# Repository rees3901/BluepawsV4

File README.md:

# Bluepaws V4

Unified firmware repository for the Bluepaws animal tracker system. Both the transmitting collar and receiving home hub share a single codebase with a common TLV binary protocol and configuration library.

## System Overview

| Component | MCU | Radio | Connectivity |
|-----------|-----|-------|-------------|
| **Collar** | nRF52840 | SX1262 LoRa | Sequans Monarch 2 GM02SP (LTE-M/NB-IoT + GNSS), BLE |
| **Home Hub** | ESP32-S3 | SX1262 LoRa | WiFi, BLE beacon |

**Data paths:**
- Collar -> LoRa -> Home Hub -> log + display -> WiFi -> Cloud
- Collar -> LTE-M/NB-IoT -> Cloud via REST POST

**Battery target:** 30+ days at 10-minute wake intervals.

## Hardware

| Part | Role | Key Specs |
|------|------|-----------|
| **nRF52840** (Seeed XIAO BLE Sense) | Collar MCU | ARM Cortex-M4F, BLE 5.0, 256KB RAM |
| **SX1262** | LoRa transceiver | 150 MHz-960 MHz, +22 dBm, LoRa/FSK |
| **[Sequans Monarch 2 GM02SP](https://sequans.com/products/monarch-2-gm02s/)** | Cellular + GNSS | LTE Cat M1/NB-IoT, integrated GNSS, 1uA deep sleep, 23 dBm TX, EAL5+ secure enclave, iSIM, single 2.2V rail, global bands |
| **ESP32-S3** (Seeed XIAO) | Hub MCU | Dual-core, WiFi, BLE 5.0, 512KB SRAM |

The Sequans GM02SP replaces the previous BG77 + L76K combination. A single module handles both cellular IoT and GPS positioning, simplifying the collar BOM and reducing power draw.

### Independent Walter LTE testbed

The separate `walter` PlatformIO target exercises real GM02SP LTE/GNSS on an
ESP32-S3 Walter board, with a simulated LoRa transmit step and its own independent
collar ID **1010**. It does not replace or alter the WisMesh collar firmware.
See [Walter setup and commissioning](docs/firmware/collar/WALTER_LTE_TESTBED.md) before provisioning
credentials or flashing. It boots idle and is not a default build/upload target.

## Repository Structure

The top level is organised by responsibility. Firmware stays under the physical
product it runs on; the two Home Hub implementations are grouped together so
that `hub` and `home-hub` no longer appear to be separate products.

```text
BluepawsV4/
├── README.md                         # Repository overview
├── docs/
│   ├── protocol/                     # Wire formats and commands
│   ├── firmware/collar/              # Collar design and test notes
│   ├── firmware/home-hub/            # Home Hub design and test notes
│   ├── operations/                   # Runbooks and release readiness
│   └── development/                  # Environment strategy and backlog
├── pcb/collar/                       # Collar PCB projects and vendor libraries
├── platformio.ini                    # Multi-environment build config
├── shared/lib/BluepawsProtocol/      # Shared protocol & config
│   ├── README.md                     # Protocol implementation notes
│   ├── library.json                  # PlatformIO library manifest
│   ├── bp_protocol.h                 # Shared protocol implementation header
│   └── bp_config.h                   # LoRa params, profiles, timing
├── collar/                           # nRF52840 collar firmware
│   ├── src/main.cpp
│   └── include/collar_pins.h
├── hub/                              # All Home Hub implementations
│   ├── platformio/                   # Heltec ESP32-S3 prototype + LittleFS UI
│   ├── esp-idf-p4/                   # ESP32-P4 production testbed
│   ├── maps/                         # Offline map-pack inputs and guidance
│   └── tests/esp-idf-p4/             # Host tests for the P4 core
├── diagnostics/
│   ├── t190-radio-monitor/           # Passive LoRa/TLV receiver (formerly sniffer)
│   └── rak3272s-bluepaws-test/       # UART2/P2P bench test and TLV heartbeat
├── tools/
│   ├── mock-server.js                # Node.js mock hub for local GUI dev
│   ├── vps_position_simulator.py     # Legacy JSON HTTPS simulator
│   ├── tlv_telemetry_simulator.py    # Headless TLV fleet simulator
│   ├── tlv_packet_codec.py           # Shared v1.2 packet/wrapper codec
│   └── tlv_simulator_gui.py          # Desktop TLV test console
├── web/                              # Next.js + TypeScript customer dashboard
│   ├── src/app/                      # App Router entry point
│   ├── src/components/               # React dashboard and Leaflet map
│   ├── src/data/                     # Typed development telemetry
│   └── src/lib/telemetry.ts          # Future Supabase adapter boundary
├── mock_server.py                    # Python mock server (legacy)
└── supabase/                         # Cloud schema, migrations, and Edge Functions
```

## Web GUI

The hub serves a real-time tracking dashboard over WiFi, built with Leaflet.js and Server-Sent Events (SSE).

**Device Cards** - each tracked animal gets a card in the left sidebar showing:
- Unique emoji avatar with colour-coded ring (auto-assigned per device)
- Last GPS coordinates in monospace
- Status badge (Home / Out / Lost / Error)
- Telemetry grid: profile, battery %, signal strength, GPS accuracy, distance from home, last seen
- **Jump** - centres map on the animal at zoom 17
- **Follow** - auto-pans the map as new positions arrive
- **Trail** - toggles breadcrumb polyline on/off per device
- **Cmd** - opens command modal

**Map Features:**
- Three base layers: Street (OSM), Satellite (Esri), Topographic
- Per-device coloured trail lines with dashed polylines
- Lost-mode markers pulse red
- Measurement tool
- Dark / light theme toggle

**Connection Monitoring:**
- Server sends SSE heartbeat every 5 seconds
- Client watchdog flips to "No heartbeat" if 10 seconds pass without any event
- Status banner shows Connected or Disconnected

## Mock Server

Simulates animals with live SSE telemetry for local GUI development:

```bash
node tools/mock-server.js
# http://localhost:3000
# Streams position updates every 2s + heartbeat every 5s
```

## Customer Web App

`web/` contains the Vercel-ready Next.js and TypeScript refactor of the hub dashboard. It preserves the embedded GUI in `hub/platformio/data/`, reads the latest live positions from Supabase by default, and confines mock telemetry to tutorial mode.

```bash
cd web
npm install
npm run dev
```

For Vercel, import this repository and select `web` as the project **Root Directory**. Leave the Install, Build, and Output settings at their detected Next.js defaults. See `web/README.md` for the exact deployment settings and the planned HTTPS Edge Function -> Supabase -> Realtime data path.

The cloud ingestion schema, device registry, and authenticated Edge Function are under `supabase/`. See `tools/VPS_SIMULATOR.md` for the Ubuntu VPS client and `tools/TLV_SIMULATOR_GUI.md` for the desktop packet-builder and manual HTTPS test console.

## Development and Production Environments

The existing Supabase `BluepawsV4` project is the permanent DEV/Test environment. Production will use a separate clean Supabase project reconstructed from the version-controlled migrations in this repository. Development and simulator data must not be migrated into production.

The same GitHub repository and Vercel project are used for both environments, with Vercel environment configuration selecting the appropriate Supabase project.

See:

- [`docs/development/DEV_TO_PROD_STRATEGY.md`](docs/development/DEV_TO_PROD_STRATEGY.md) for the authoritative promotion strategy and decision record.
- [`docs/development/ENVIRONMENT_MATRIX.md`](docs/development/ENVIRONMENT_MATRIX.md) for DEV vs PROD separation rules.
- [`docs/operations/PRODUCTION_READINESS_CHECKLIST.md`](docs/operations/PRODUCTION_READINESS_CHECKLIST.md) for the pre-launch security and operational checklist.

## TLV Protocol v1.2

The canonical protocol document is:

```text
docs/protocol/TLV_PROTOCOL_V1_2.md
```

The system is moving away from production JSON telemetry. JSON remains useful for debugging, logs, exports and admin APIs, but LoRa and cellular telemetry should use the compact binary TLV packet.

Locked packet shape:

```text
[32-byte fixed header][0-24 bytes TLV][8-byte HMAC-SHA256 tag]
```

Packet size:

```text
minimum = 40 bytes
maximum = 64 bytes
```

### Fixed header summary

| Offset | Size | Field | Type | Notes |
|---:|---:|---|---|---|
| 0 | 1 | `ver` | u8 | Protocol version |
| 1 | 2 | `device_guid16` | u16 | Immutable collar identity |
| 3 | 2 | `msg_seq_id` | u16 | Per-device rolling sequence |
| 5 | 4 | `time_unix` | u32 | UTC timestamp |
| 9 | 1 | `state` | u8 | Packed status + power profile |
| 10 | 1 | `flags` | u8 | Core bitfield |
| 11 | 1 | `tx_reason` | u8 | Transmission reason enum |
| 12 | 4 | `lat_e7` | i32 | Latitude x 10000000 |
| 16 | 4 | `lon_e7` | i32 | Longitude x 10000000 |
| 20 | 2 | `batt_mV` | u16 | Battery voltage |
| 22 | 2 | `acc_m` | u16 | Accuracy in metres |
| 24 | 2 | `fix_age_s` | u16 | GNSS fix age |
| 26 | 1 | `sat_count` | u8 | Satellite count |
| 27 | 4 | `hdr_rsvd` | u8[4] | Reserved, set 0 |
| 31 | 1 | `tlv_len` | u8 | 0-24 TLV bytes |

The 8-byte tag is the first eight bytes of HMAC-SHA256 over the complete header
and TLV section. The same authenticated binary packet is preserved across LoRa
and LTE paths; path-specific RF and gateway details live only in the HTTPS JSON
wrapper. See the canonical document for enums, selected TLVs, validation rules
and examples.

## Message Flow

```text
Collar --LoRa--> Hub --REST POST--> Cloud
Collar --LTE-M/Cat-M1 REST POST--> Cloud
```

Both paths preserve the original authenticated packet, including `(device_guid16, msg_seq_id, time_unix)`. The hub relays the collar bytes without changing them. Redundancy is intentional for reliability.

Canonical retry deduplication is handled in the cloud using:

```text
SHA-256(complete authenticated packet)
```

Reuse of `(device_guid16, msg_seq_id, time_unix)` with different packet content
is treated as an identity conflict rather than an overwrite.

Hub CSV or debug log format should be derived from decoded TLV fields, not treated as the production on-air format.

## Building

Requires [PlatformIO](https://platformio.org/).

```bash
# Build both targets
pio run

# Build collar only
pio run -e collar

# Build hub only
pio run -e hub

# Upload to connected device
pio run -e collar -t upload
pio run -e hub -t upload
```

## Operating Profiles

| Profile | TX Power | Interval | Cellular | Remarks |
|---------|----------|----------|----------|---------|
| **Normal** | 19 dBm | 10 min | 1:10 | Daily tracking, balanced power and update frequency |
| **PowerSave** | 10 dBm | 30 min | 1:30 | At home or battery conservation, reduced TX power and longer sleep |
| **Active Find** | 19 dBm | 1 min | 1:5 | Cat is outside geofence or user is actively searching |
| **Emergency Lost** | 22 dBm | 30 s | 1:3 | User needs frequent updates for retrieval, then fallback to Active Find |

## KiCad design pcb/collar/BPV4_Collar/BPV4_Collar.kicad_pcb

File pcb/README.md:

# PCB Hardware

KiCad projects and their supporting component models are grouped by product.

For GM02SP, GNSS/LTE antenna, and modem power decisions, start with the
[Walter/GM02SP source guide](../docs/firmware/collar/WALTER_GM02SP_UPSTREAM_REFERENCE.md).
Its Walter board specifications must be checked against the bare GM02SP and the
production collar schematic before being used as PCB requirements.

The approved forward power design is the
[nPM1300 collar power architecture](../docs/hardware/collar/NPM1300_POWER_ARCHITECTURE.md).
It replaces the BQ24074, TPS62840 and MAX17048 architecture still present in the
current KiCad schematic; follow its verification gates during migration.

- `collar/` — BluePaws V4 collar main board, second board, evaluation layouts,
  plots, reports, symbols, footprints, 3D models, and retained vendor source
  packages.

The vendor assets have deliberately been retained. Some appear duplicated
because they preserve the original package or tool format used by an existing
KiCad project; deduplication should only happen after KiCad library references
are audited interactively.

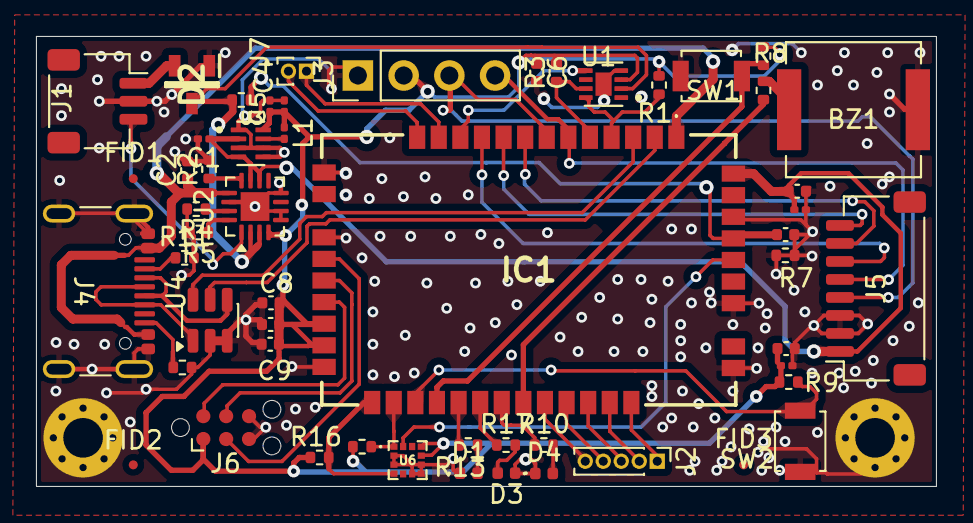
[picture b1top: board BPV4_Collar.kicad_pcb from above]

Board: 2 copper layers, 50.0 x 25.0 mm, 56 parts (0 on the bottom side), 49 nets.

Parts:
BZ1: CPT-7502-65-SMT-TR; XDCR_CPT-7502-65-SMT-TR
C1: C 10uF; C_0201_0603Metric
C2, C8: 1uF; C_0402_1005Metric
C3, C9, C10, C12, C13: 100nF; C_0402_1005Metric
C4, C5, C11, C14: 10uF; C_0201_0603Metric
C6: C 100nF; C_0402_1005Metric
D1, D3, D4: LED; LED_0402_1005Metric
D2: DMG2305UX-13; SOT96P240X120-3N
FID1, FID2, FID3: Fiducial; Fiducial_0.5mm_Mask1mm
IC1: RAK4630
J1: Conn_01x03; JST_SH_SM03B-SRSS-TB_1x03-1MP_P1.00mm_Horizontal
J2: Conn_01x05; PinHeader_1x05_P1.00mm_Vertical
J3: Conn_01x04; PinHeader_1x04_P2.54mm_Vertical
J4: USB_C_Receptacle_USB2.0_14P; USB_C_Receptacle_GCT_USB4105-xx-A_16P_TopMnt_Horizontal
J5: Conn_01x08; JST_SH_SM08B-SRSS-TB_1x08-1MP_P1.00mm_Horizontal
J6: Conn_01x06; Tag-Connect_TC2030-IDC-NL_2x03_P1.27mm_Vertical
J7: Conn_01x02_Pin; PinHeader_1x02_P1.00mm_Vertical
L1: 2.2uH; L_0201_0603Metric
MH1, MH2: M2_Screw; MountingHole_2.2mm_M2_Pad_Via
R1, R3: 4.7k; R_0402_1005Metric
R2, R5, R10, R13, R14, R17: 1k; R_0402_1005Metric
R4, R8, R9, R15, R16: 10k; R_0402_1005Metric
R6, R7: 1M; R_0402_1005Metric
R11, R12: 5.1k; R_0402_1005Metric
SW1, SW2: SW_Push; SW_SPST_B3U-1000P
U1: MAX17048G_T10; SON50P200X200X80-9N
U2: BQ24074RGT; VQFN-16-1EP_3x3mm_P0.5mm_EP1.6x1.6mm
U3: TPS62840DLCR; SON50P200X150X100-8N
U4: USBLC6-2SC6; SOT-23-6
U6: LIS2DW12TR; LGA12R50P4X4_200X200X70

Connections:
Accel: IC1.40 (P0.05/AIN3), U6.12 (INT1)
BATT_ALERT: IC1.11 (P0.21/UART1_DE), U1.5 (~ALERT)
BATT_I2C_SCL: IC1.5 (P0.14/I2C_SCL), R3.1, U1.7 (SCL)
BATT_I2C_SDA: IC1.4 (P0.13/I2C_SDA), R1.2, U1.8 (SDA)
BATT_NTC: J1.3, U2.1 (TS)
GM02SP_PS_STATUS: IC1.10 (P0.20/UART1_TX_(AT_COMMAND)), J5.6
GM02SP_RESET: IC1.9 (P0.19/UART1_RX_(AT_COMMAND)), J5.8
GND: BZ1.1, C1.2, C2.2, C3.2, C4.2, C5.2, C6.2, C8.2, C9.2, C10.2, C11.2, C12.2, C13.2, C14.2, D1.1 (K), D2.1 (G), D3.1 (K), D4.1 (K), IC1.14 (GND_1), IC1.16 (GND_2), IC1.22 (GND_3), IC1.36 (GND_5), IC1.38 (GND_6), IC1.42 (GND_7), J1.2, J3.1, J4.A1 (GND), J4.A12 (GND), J4.B1 (GND), J4.B12 (GND), J4.S1 (SHIELD), J5.2, J5.3, J6.5, J6.6, MH1.1, MH2.1, R2.2, R4.2, R5.2, R7.1, R7.2, R11.2, R12.2, SW1.2 (A), SW2.1 (K), U1.4 (GND), U1.9 (EP), U2.5 (EN2), U2.6 (EN1), U2.8 (VSS), U2.14 (TMR), U2.17 (VSS), U3.1 (GND), U3.3 (MODE), U3.5 (VSET), U3.6 (STOP), U4.2 (GND), U4.3 (I/O2), U6.2 (CS), U6.3 (SDO/SA0), U6.6 (GND), U6.7 (RES), U6.8 (GND)
NRF_RESET: IC1.17 (NRF_RESET), J6.3
unnamed: BZ1.2, R14.2
unnamed: D1.2 (A), R13.2
unnamed: D3.2 (A), R17.2
unnamed: D4.2 (A), R10.2
unnamed: IC1.35 (GND_4), J2.1
unnamed: IC1.30 (P0.02/QSPI_DIO3), R14.1
unnamed: IC1.29 (P0.03/QSPI_CLK), R10.1
unnamed: IC1.13 (P0.09/NFC1), J7.2
unnamed: IC1.12 (P0.10/NFC2), J7.1
unnamed: IC1.23 (P0.24/I2C_SDA_2), R16.2, U6.4 (SDA/SDI/SDO)
unnamed: IC1.24 (P0.25/I2C_SCL_2), R15.2, U6.1 (SCL/SPC)
unnamed: IC1.34 (P0.26/QSPI_CS), J2.2
unnamed: IC1.31 (P0.28/QSPI_DIO2), J2.5
unnamed: IC1.32 (P0.29/QSPI_DIO1), J2.4
unnamed: IC1.33 (P0.30/QSPI_DIO0), J2.3
unnamed: IC1.25 (P1.01/SW1), R9.2, SW2.2 (A)
unnamed: IC1.26 (P1.02/SW2), R8.2, SW1.1 (K)
unnamed: IC1.27 (P1.03/LED1), R13.1
unnamed: IC1.28 (P1.04/LED2), R17.1
unnamed: J4.A5 (CC1), R11.1
unnamed: J4.B5 (CC2), R12.1
unnamed: J4.A6 (D+), J4.B6 (D+), U4.1 (I/O1)
unnamed: J4.A7 (D-), J4.B7 (D-), U4.4 (I/O2)
unnamed: R2.1, U2.12 (ILIM)
unnamed: R5.1, U2.16 (ISET)
unnamed: R4.1, U2.15 (ITERM)
unnamed: L1.2, U3.7 (SW)
SWDCLK: IC1.18 (SWDCLK), J6.4
SWDIO: IC1.19 (SWDIO), J6.2
UART_RX: IC1.6 (P0.15/UART2_RX), J3.4, J5.5
UART_TX: IC1.7 (P0.16/UART2_TX), J3.3, J5.4
USB_D+: IC1.3 (USB+), U4.6 (I/O1)
USB_D-: IC1.2 (USB-), U4.5 (VBUS)
VBAT: D2.3 (D), R6.2, U1.2 (CELL), U2.2 (BAT), U2.3 (BAT)
VBAT_RAW+: D2.2 (S), J1.1
VBAT_SENSE: C3.1, IC1.41 (P0.04/AIN2), R6.1
VBUS_5V: C2.1, IC1.1 (VBUS), J4.A4 (VBUS), J4.A9 (VBUS), J4.B4 (VBUS), J4.B9 (VBUS), U2.13 (IN)
VCC_3v3: C4.1, C5.1, C6.1, C8.1, C9.1, C10.1, C13.1, C14.1, IC1.20 (VBAT_SX), IC1.21 (VBAT_IO_SX), J3.2, J6.1, L1.1, R1.1, R3.2, R8.1, R9.1, R15.1, R16.1, U1.3 (VDD), U2.4 (~CE), U3.8 (VOS), U6.9 (VDD), U6.10 (VDDIO)
VOUT_SYS: C1.1, C11.1, C12.1, IC1.44 (VBAT_NRF), J5.1, U2.10 (OUT), U2.11 (OUT), U3.2 (VIN), U3.4 (EN)
WAKE: IC1.8 (P0.17/UART2_DE), J5.7

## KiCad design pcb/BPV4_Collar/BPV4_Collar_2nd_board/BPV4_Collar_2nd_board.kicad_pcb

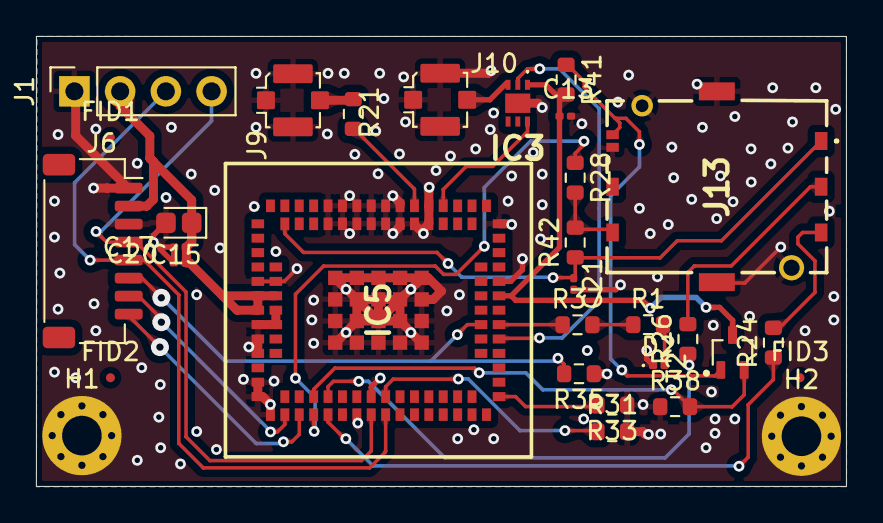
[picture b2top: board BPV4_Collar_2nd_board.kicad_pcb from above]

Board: 2 copper layers, 45.0 x 25.0 mm, 31 parts (0 on the bottom side), 27 nets.

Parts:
C13: 100 nF; C_0201_0603Metric
C15: 220 uF; CP_EIA-1608-08_AVX-J
C17: 10uF; C_0201_0603Metric
C20, C21: 100nF; C_0201_0603Metric
D2: LED; LED_0201_0603Metric
FID1, FID2, FID3: Fiducial; Fiducial_0.5mm_Mask1mm
H1, H2: MountingHole_Pad; MountingHole_2.2mm_M2_Pad_Via
IC3: SKY65723-11; SKY6572311
IC5: GM02SP
J1: Conn_01x04; PinSocket_1x04_P2.54mm_Vertical
J6: Conn_01x08; JST_SH_SM08B-SRSS-TB_1x08-1MP_P1.00mm_Horizontal
J9, J10: CONUFL001-SMD-T; U.FL_Molex_MCRF_73412-0110_Vertical
J13: SIM8055-6-1-14-00-A; SIM8055611401A
R1, R21: 0R; R_0603_1608Metric
R24: 22R; R_0603_1608Metric
R26, R28: 22O; R_0603_1608Metric
R31, R37: 1k; R_0603_1608Metric
R33, R35, R38, R41: 100k; R_0603_1608Metric
R42: 4.7k; R_0603_1608Metric
T2: NX3008PBKMB; SOT65P210X110-3N

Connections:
1V8_OUT: C13.1, IC3.1 (VCC), IC5.8 (1V8), R41.2, T2.3
GND: C13.2, C15.2, C17.2, C20.2, C21.2, D2.1 (K), H1.1, H2.1, IC3.7 (EP), IC5.1 (GND_1), IC5.6 (GND_2), IC5.37 (GND_3), IC5.38 (GND_4), IC5.50 (GND_5), IC5.51 (GND_6), IC5.52 (GND_7), IC5.54 (GND_8), IC5.56 (GND_9), IC5.58 (GND_10), IC5.59 (GND_11), IC5.61 (GND_12), IC5.64 (GND_13), IC5.65 (GND_14), IC5.78 (GND_15), IC5.79 (GND_16), IC5.80 (GND_17), IC5.81 (GND_18), IC5.82 (GND_19), IC5.83 (GND_20), IC5.84 (GND_21), IC5.85 (GND_22), IC5.86 (GND_23), IC5.87 (GND_24), IC5.88 (GND_25), IC5.89 (GND_26), IC5.91 (GND_27), IC5.92 (GND_28), IC5.93 (GND_29), IC5.G1 (GND_30), IC5.G2 (GND_31), IC5.G3 (GND_32), IC5.G4 (GND_33), IC5.G5 (GND_34), IC5.G6 (GND_35), IC5.G7 (GND_36), IC5.G8 (GND_37), IC5.G9 (GND_38), IC5.G10 (GND_39), IC5.G11 (GND_40), IC5.G12 (GND_41), IC5.G13 (GND_42), IC5.G14 (GND_43), IC5.G15 (GND_44), IC5.G16 (GND_45), IC5.G17 (GND_46), IC5.G18 (GND_47), IC5.G19 (GND_48), IC5.G20 (GND_49), J1.1, J6.1, J6.3, J9.2 (GND_1), J10.2 (GND_1), J13.C5 (GND), J13.MH1, J13.MH2, J13.MP1, J13.MP2, R31.1, R33.1, R35.1, R38.1
GNSS_EN: IC3.2 (VEN), IC5.14 (GPIO28/_DTR0)
GNSS_RF: IC3.6 (RF_OUT), IC5.94 (DNC_9)
LTE_ANT: IC5.90 (LTE_ANT), R21.2
unnamed: D2.2 (A), R1.2
unnamed: IC3.3 (RF_IN), J10.1 (SIG)
unnamed: IC5.12 (GPIO1/_STATUS_LED), R37.1
unnamed: IC5.35 (GPIO14/CTS0), R31.2
unnamed: IC5.20 (RESERVED/_FFF_FFH), R33.2
unnamed: IC5.42 (SIM0_CLK), R24.1
unnamed: IC5.44 (SIM0_IO), R28.1
unnamed: IC5.43 (SIM0_RSTN), R26.1
unnamed: J9.1 (SIG), R21.1
unnamed: J13.CD1, R41.1, T2.1
unnamed: R1.1, R37.2
PS_STATUS: IC5.13 (GPIO2/_PS_STATUS), J6.6, R35.2
RESETN: IC5.46 (RESETN), J6.8
SIM_CLK: J13.C3 (CLK), R24.2
SIM_DETECT: IC5.45 (SIM0_DETECT), R38.2, T2.2
SIM_IO: J13.C7 (I/O), R28.2, R42.2
SIM_RESET: J13.C2 (RST), R26.2
UART0_RX: IC5.34 (GPIO13/RXD0), J1.3, J6.5
UART0_TX: IC5.36 (GPIO12/TXD0), J1.4, J6.4
VBAT: C15.1, C17.1, C20.1, IC5.60 (VBAT_1), IC5.62 (VBAT_2), IC5.63 (VBAT_3), J1.2, J6.2
VSIM: C21.1, IC5.73 (SIM0_VCC), J13.C1 (VCC), R42.1
WAKE0: IC5.48 (WAKE0), J6.7
